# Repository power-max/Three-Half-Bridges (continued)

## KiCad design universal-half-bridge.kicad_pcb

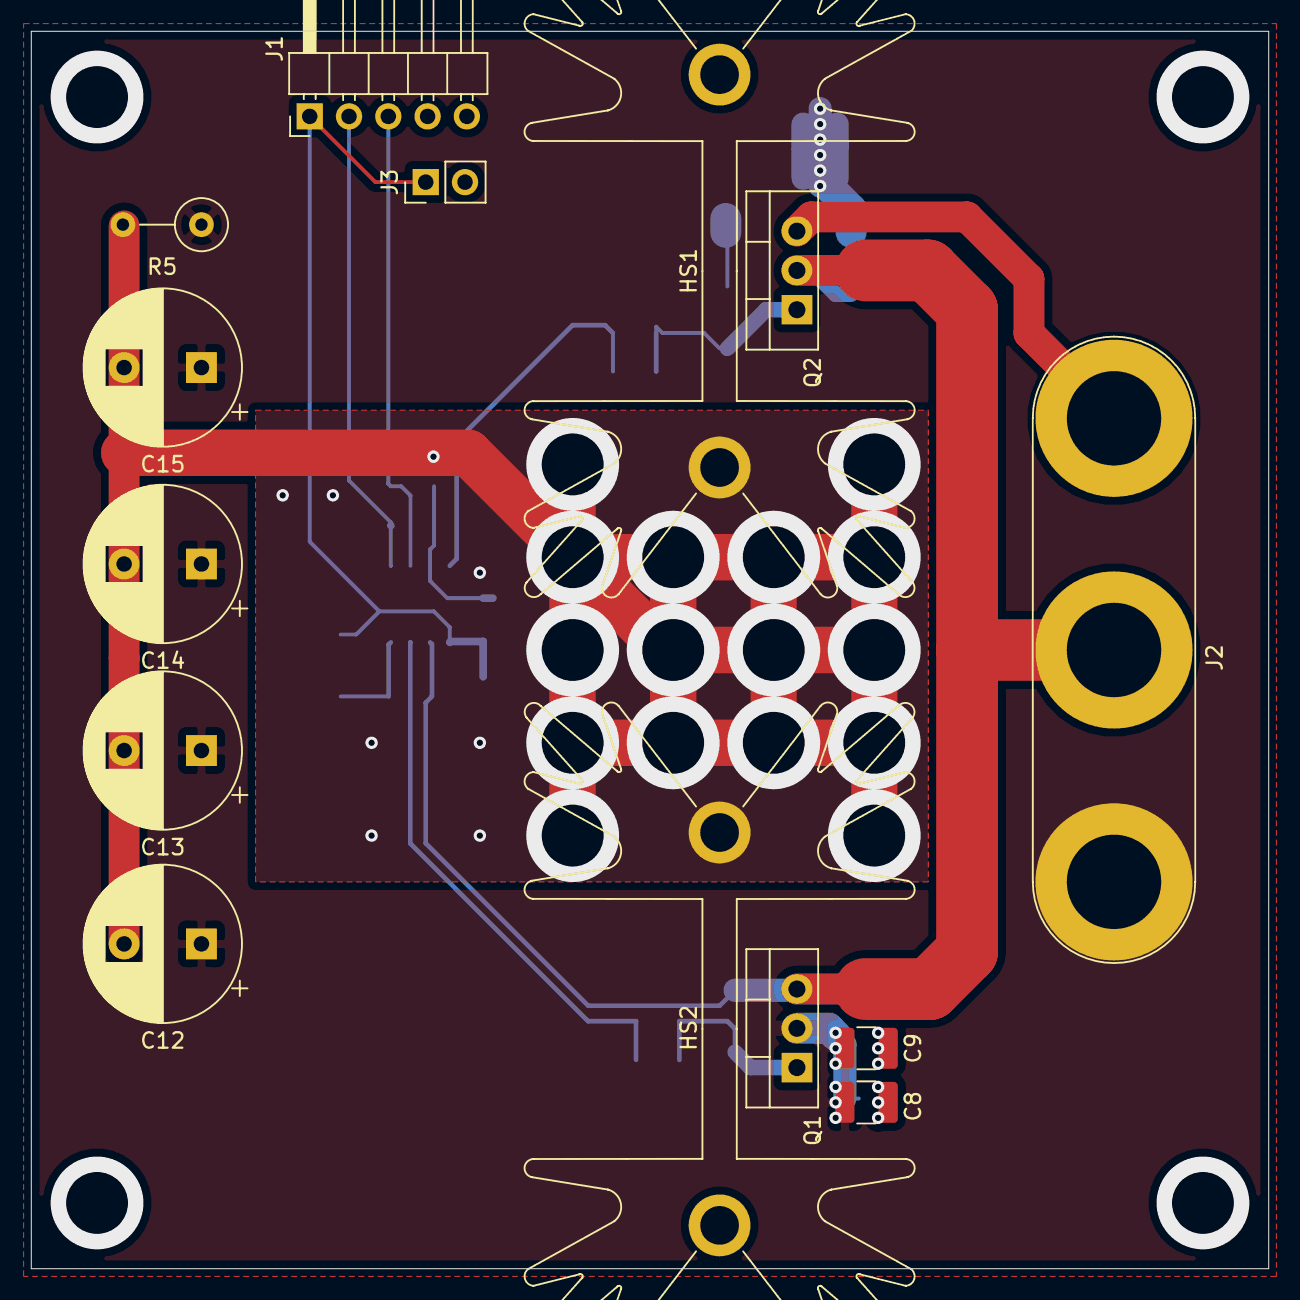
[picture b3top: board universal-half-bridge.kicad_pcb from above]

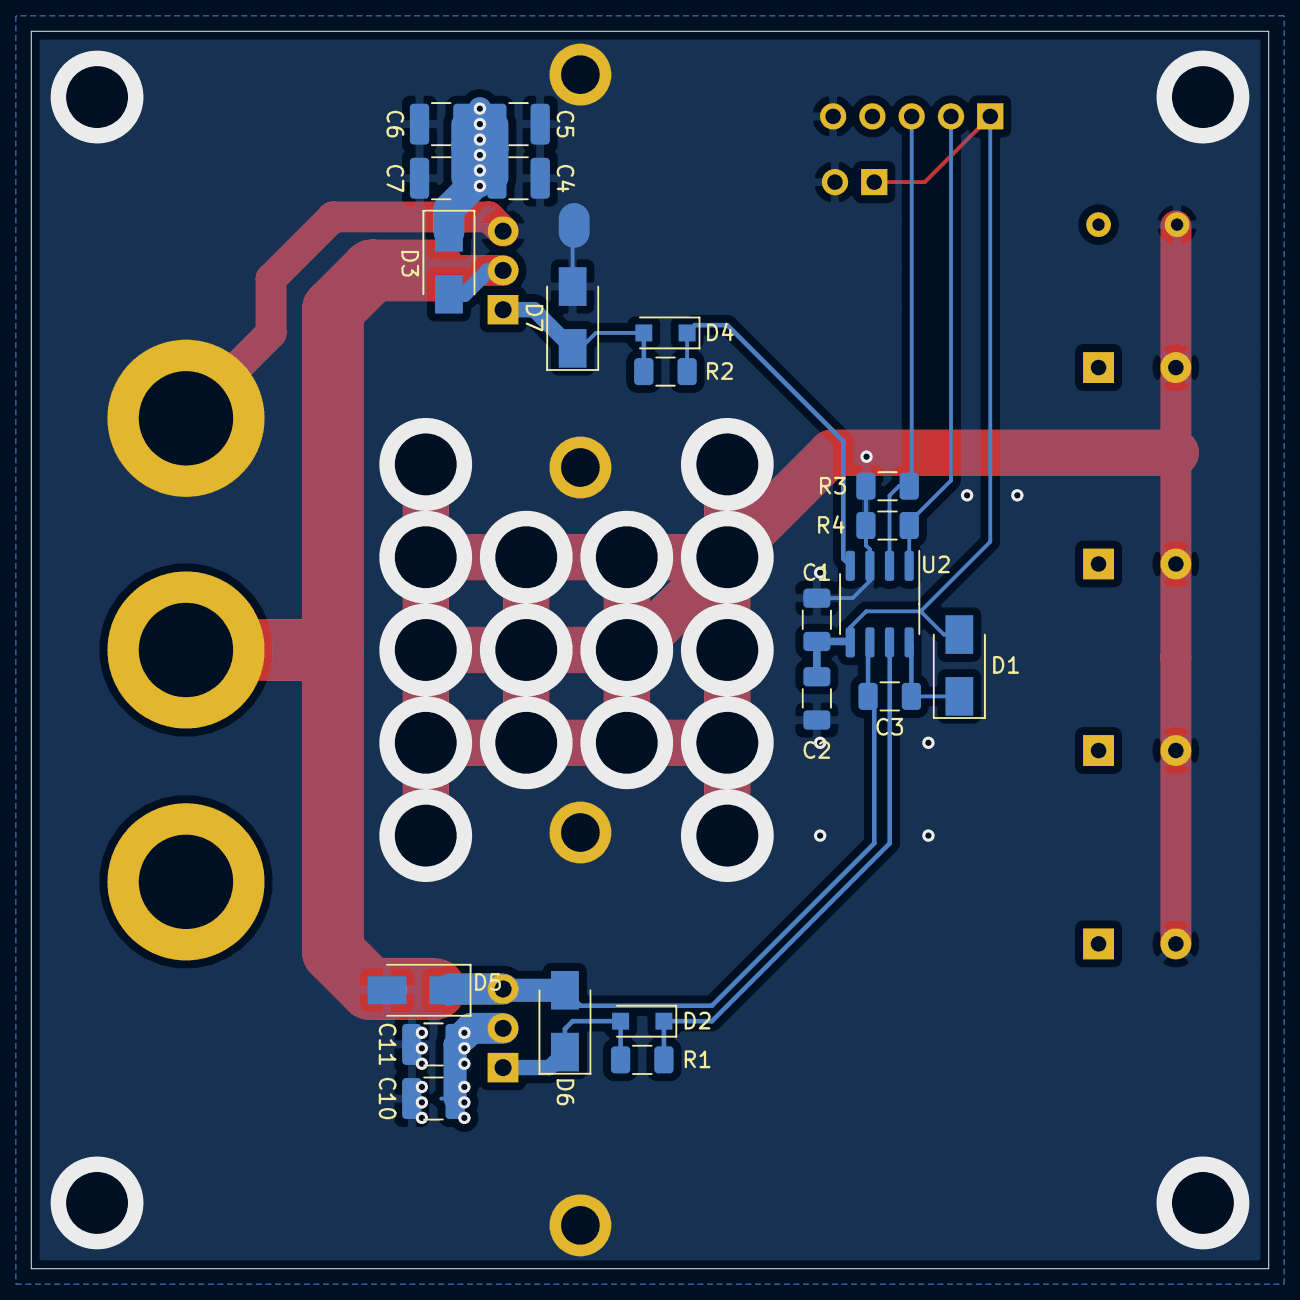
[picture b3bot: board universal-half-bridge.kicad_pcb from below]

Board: 2 copper layers, 80.0 x 80.0 mm, 35 parts (21 on the bottom side), 11 nets.

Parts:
C1, C2: 100nF; R_1206_3216Metric
C3: 1uF; C_1206_3216Metric
C4, C5, C6, C7, C8, C9, C10, C11: 100n; C_1210_3225Metric
C12, C13, C14, C15: 100uF; CP_Radial_D10.0mm_P5.00mm
D1, D3, D5: D; D_SMA
D2, D4: D; D_SOD-123F
D6, D7: D_TVS; D_SMA
HS1, HS2: Heatsink_Pad; Heatsink_Fischer_SK129-STS_42x25mm_2xDrill2.5mm
J1: Conn_01x05_Male; PinHeader_1x05_P2.54mm_Horizontal
J2: Conn_01x03_Female; Banana_Jack_3Pin
J3: Conn_01x02_Female; PinHeader_1x02_P2.54mm_Vertical
Q1, Q2: Q_NMOS_GDS; TO-220-3_Vertical
R1, R2: 10; R_1206_3216Metric
R3, R4: 1k; R_1206_3216Metric
R5: 1000; R_Axial_DIN0309_L9.0mm_D3.2mm_P5.08mm_Vertical
U2: IRS2186; SOIC-8_3.9x4.9mm_P1.27mm

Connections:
+12V: C1.1, C2.1, D1.2, J1.1, J3.1, U2.5
GND: C1.2, C2.2, C4.1, C5.1, C6.1, C7.1, C8.1, C9.1, C10.1, C11.1, C12.2, C13.2, C14.2, C15.2, D5.2, D7.2, HS1.1, HS2.1, J1.5, J2.3, J3.2, Q2.3, R3.1, R4.2, R5.2, U2.3
unnamed: C3.1, D3.2, D5.1, D6.2, J2.2, Q1.3, Q2.2, U2.6
unnamed: C3.2, D1.1, U2.8
unnamed: D2.1, R1.2, U2.7
unnamed: D2.2, D6.1, Q1.1, R1.1
unnamed: D4.1, R2.2, U2.4
unnamed: D4.2, D7.1, Q2.1, R2.1
unnamed: J1.2, R4.1, U2.1
unnamed: J1.3, R3.2, U2.2
VCC: C4.2, C5.2, C6.2, C7.2, C8.2, C9.2, C10.2, C11.2, C12.1, C13.1, C14.1, C15.1, D3.1, J2.1, Q1.2, R5.1

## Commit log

2020-09-15 added KiCAD files
2022-08-11 Update README.md
    readme updated to reflect soon to come changes.
2022-08-11 Update README.md
    title
2022-08-12 Massive overhaul including a change in the scope of the project! Yeah I know this goes against the "atomic commits" philosophy of git, don't @ me!
2022-08-12 added .gitignore file
2022-08-12 deleted all temporary and export files as per .gitignore file sourced from https://github.com/github/gitignore.
2023-01-17 cleanup (removed KiCad v5 legacy files)
2023-01-17 added/corrected placeholder resistor values
2023-01-17 added infomation to title block, generated PDF of schematic
2023-01-17 updated gerber exports
2024-11-10 about to do some amazing shit, actaully update my funcikng project!
2024-11-10 updated the 3 half bridges project, the dodgybrothers positive negative SR latch idea turned out to be retarded and didn't work at all.
2024-11-25 Updated LDO footrprint to use the SOT89 LM78L05 (issue 10); moved high side local regulators closer to digital isolator ICs (issue 10); pushed digital isolator ICs further to the allow room for LRs (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
2024-11-25 turned into a 4 layer board for improved EMI and lower parasitics, should still be 100% compatible as a 2 layer board!
2024-11-25 moved silkscreen for HVDC input and added additional 5VDC for the low voltage primary input
2024-11-25 forgot to save and close prior to last commit
2024-11-25 updated footprint for terminal blocks to use AMT0450028DB0000G‎
2024-11-25 added pdf exports
2024-11-25 Delete ~three_half_bridges.kicad_pcb.lck
    not sure why this got added to the staging area, may need to update .gitignore
2024-11-25 fixed the accidentally flipped terminal block posistive terminal
2024-12-23 beginings of the implementation of the 10 open issues
2025-03-26 fixed many issues from previous itteration, added design rule checks to enforce minumum 2mm clearence between LV and HV side
2025-03-26 updated PDF export schematics
